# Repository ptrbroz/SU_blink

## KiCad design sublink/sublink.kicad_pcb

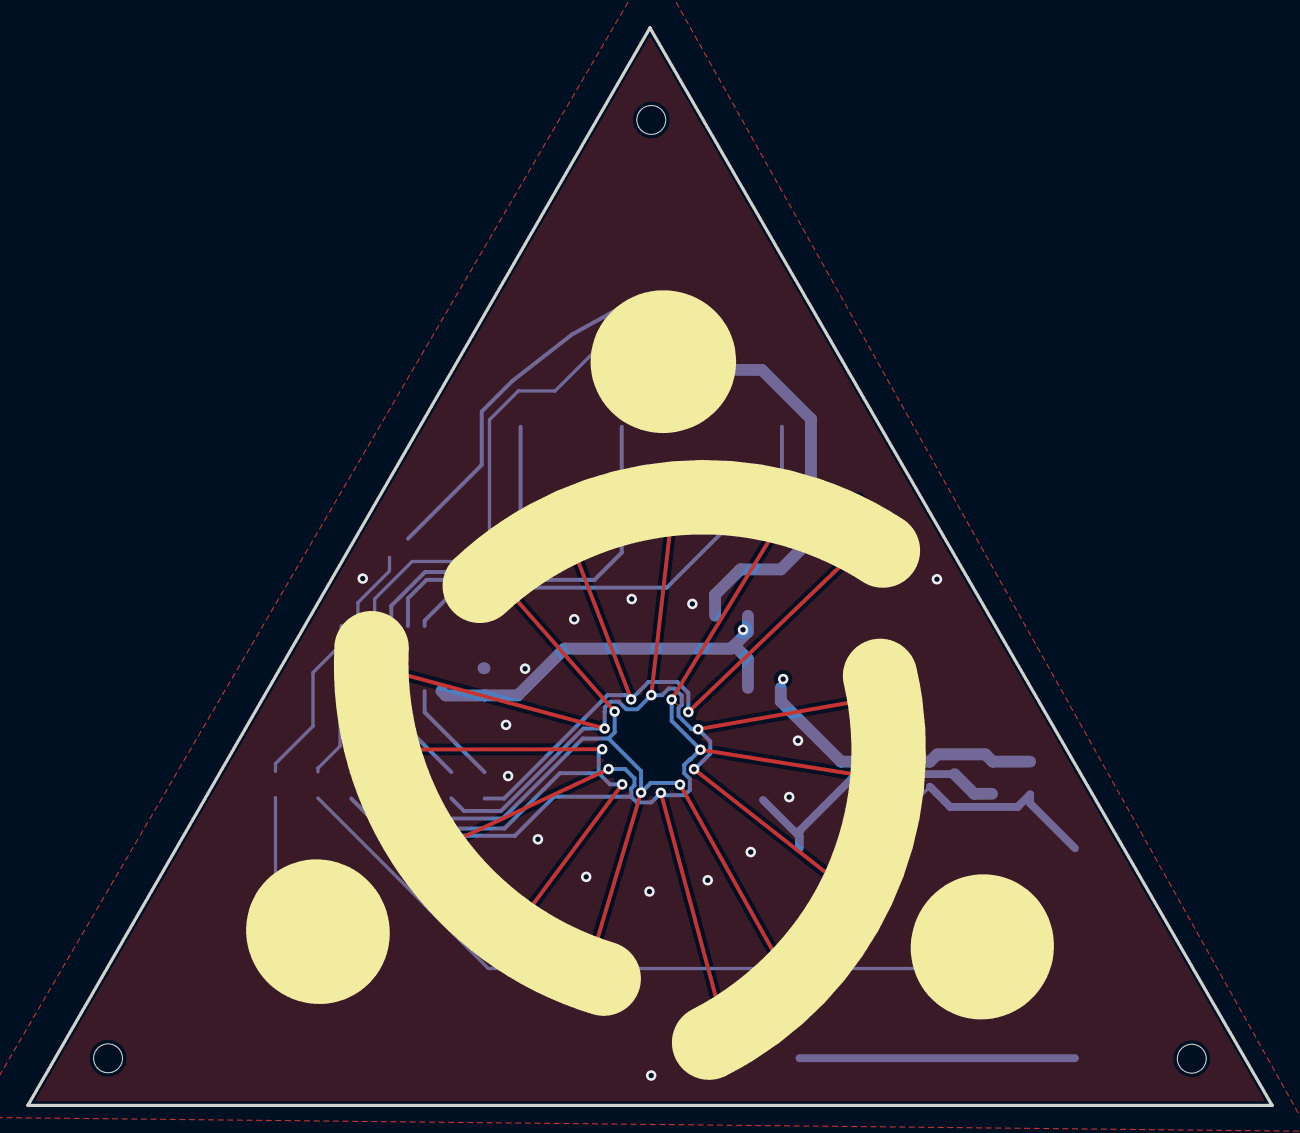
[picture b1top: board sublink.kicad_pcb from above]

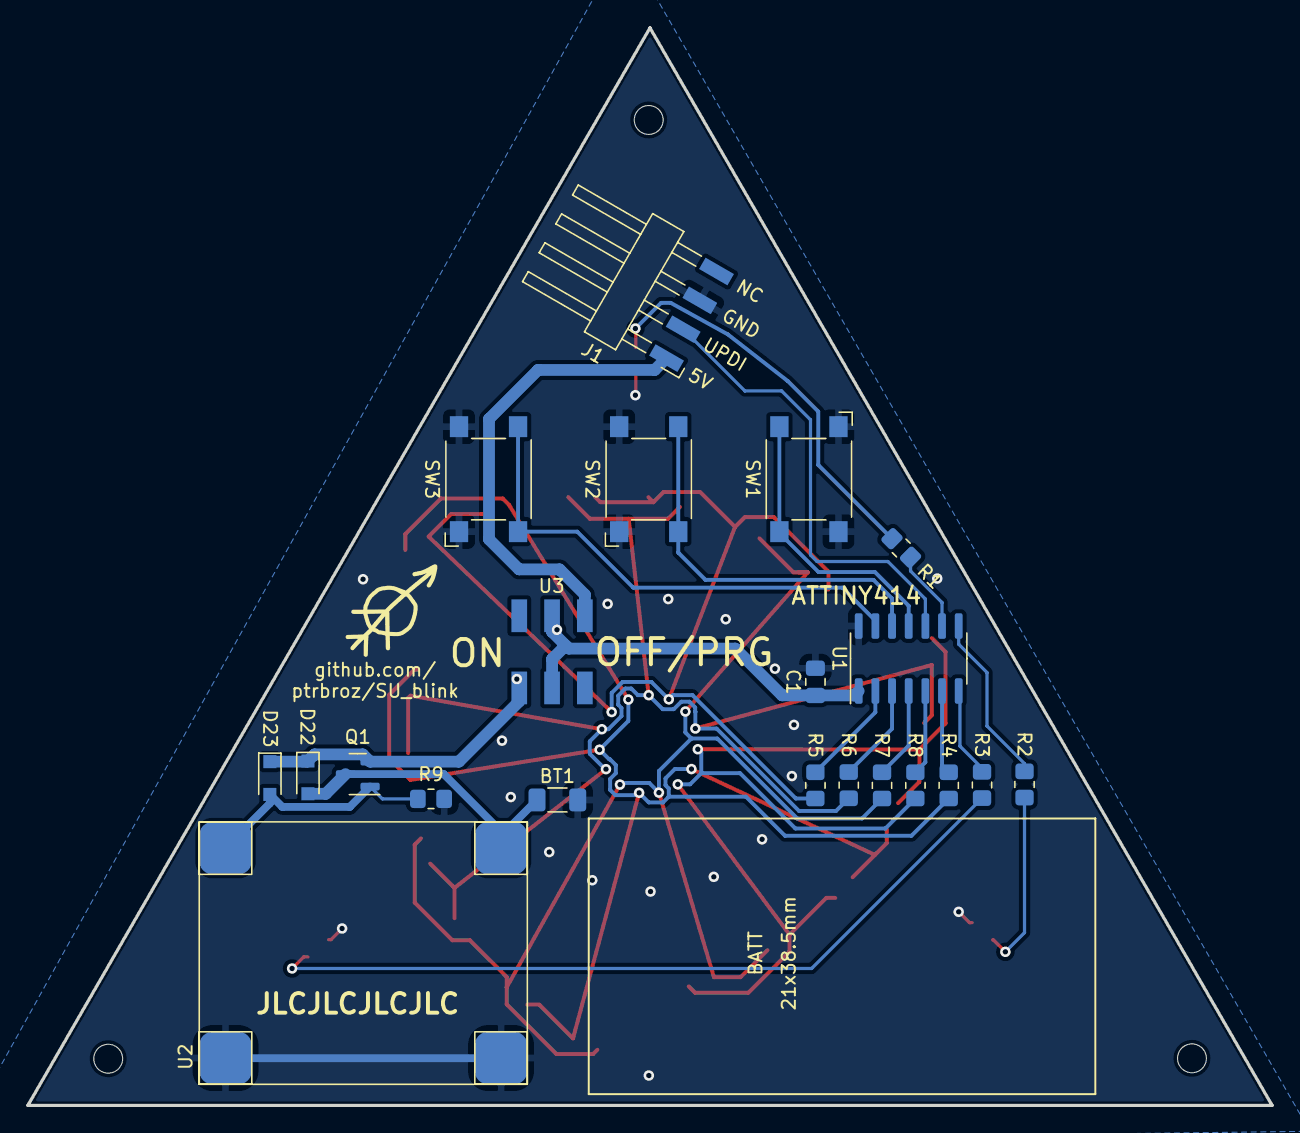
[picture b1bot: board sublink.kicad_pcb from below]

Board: 2 copper layers, 94.8 x 82.1 mm, 45 parts (21 on the bottom side), 26 nets.

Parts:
BT1: 3V7; R_1206_3216Metric_Pad1.30x1.75mm_HandSolder
C1: 100n; C_0805_2012Metric_Pad1.18x1.45mm_HandSolder
D1, D2, D3: LED; LED_0805_2012Metric_Pad1.15x1.40mm_HandSolder
D4, D5, D6, D7, D8, D9, D10, D11, D12, D13, D14, D15, D16, D17, D18, D19, D20, D21: LED_Small; LED_0805_2012Metric_Pad1.15x1.40mm_HandSolder
D22: DNP; D_SOD-323_HandSoldering
D23: BAS21HT1G; D_SOD-323_HandSoldering
H1, H2, H3: MountingHole; MountingHole_2.2mm_M2
J1: ZL315-4SGH; Harwin_M20-89004xx_1x04_P2.54mm_Horizontal
Q1: Q_PMOS_GSD; SOT-23
R1, R2, R3, R4, R5, R6, R7, R8: R_Small; R_0805_2012Metric_Pad1.20x1.40mm_HandSolder
R9: 10k; R_0805_2012Metric_Pad1.20x1.40mm_HandSolder
SW1, SW2, SW3: SW_Push; SW_SPST_Omron_B3FS-100xP
U1: ATtiny414-SS; SOIC-14_3.9x8.7mm_P1.27mm
U2: OKY3402
U3: JS202011

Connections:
GND: BT1.2 (-), C1.2, D1.1 (K), D2.1 (K), D3.1 (K), J1.3, R9.1, SW1.1, SW2.1, SW3.1, U1.14 (GND), U2.1 (USB-), U2.3 (B-)
L0: D4.2 (A), D5.1 (K), D6.1 (K), D7.2 (A), D8.1 (K), D9.2 (A), R5.1
L1: D6.2 (A), D7.1 (K), D10.1 (K), D11.2 (A), D12.1 (K), D13.2 (A), D20.1 (K), D21.2 (A), R6.1
L2: D8.2 (A), D9.1 (K), D10.2 (A), D11.1 (K), D14.1 (K), D15.2 (A), D18.1 (K), D19.2 (A), R4.1
L3: D4.1 (K), D5.2 (A), D12.2 (A), D13.1 (K), D14.2 (A), D15.1 (K), D16.1 (K), D17.2 (A), R7.1
L4: D16.2 (A), D17.1 (K), D18.2 (A), D19.1 (K), D20.2 (A), D21.1 (K), R8.1
unnamed: BT1.1 (+), D22.2 (A), Q1.3 (D), U2.4 (B+)
unnamed: D1.2 (A), R1.2
unnamed: D22.1 (K), D23.1 (K), Q1.2 (S), U3.6
unnamed: D23.2 (A), Q1.1 (G), R9.2, U2.2 (USB+)
unnamed: R1.1, U1.9 (PB0)
unnamed: R2.1, U1.8 (PB1)
unnamed: D3.2 (A), R2.2
unnamed: R3.1, U1.7 (PB2)
unnamed: D2.2 (A), R3.2
unnamed: R4.2, U1.6 (PB3)
unnamed: R5.2, U1.2 (PA4)
unnamed: R6.2, U1.3 (PA5)
unnamed: R7.2, U1.4 (PA6)
unnamed: R8.2, U1.5 (PA7)
unnamed: J1.1, U3.1
UPDI: J1.2, U1.10 (~RESET/PA0)
VCC: C1.1, U1.1 (VCC), U3.2, U3.5
butt1: SW1.2, U1.11 (PA1)
butt2: SW2.2, U1.12 (PA2)
butt3: SW3.2, U1.13 (PA3)

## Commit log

2022-11-17 wip first pass schematic
2022-11-20 wip schematic probably done
2022-11-24 wip board outline, led placement
2022-11-24 wip bottom side component positioning
2022-11-24 first pass all components placement
2022-11-24 ignore kicad backups
2022-11-26 wip routing
2022-11-26 wip top radial routing
2022-11-28 bottom circle routing. Broke chargin part footprint for some reason
2022-11-28 dot routing
2022-11-29 finishing touches, silkscreen etc
2022-12-01 fabrication files
2022-12-11 add wip platformio, arduino programs, fusion model for 3D print
2022-12-12 more readable led numbering
2022-12-14 animation infrasctructure, first animation
2022-12-19 wip animations and reconfigurability
2022-12-19 working, configurable running dot
2022-12-20 working pendulum clock
2022-12-20 pulsing light anim
2022-12-20 stacking dots animation
2022-12-21 rewrite modification logic to be handled for all animations in handleModButton and handleModify
2022-12-21 remove deprecated anim arguments, some leftover mod code in stacked dots
2022-12-21 fix bug related to modstate overflow, fix bug in modifying direction of stacked dots
2022-12-22 marker eraser animation
2022-12-22 add hold support to modify
2022-12-23 change initial conditions
